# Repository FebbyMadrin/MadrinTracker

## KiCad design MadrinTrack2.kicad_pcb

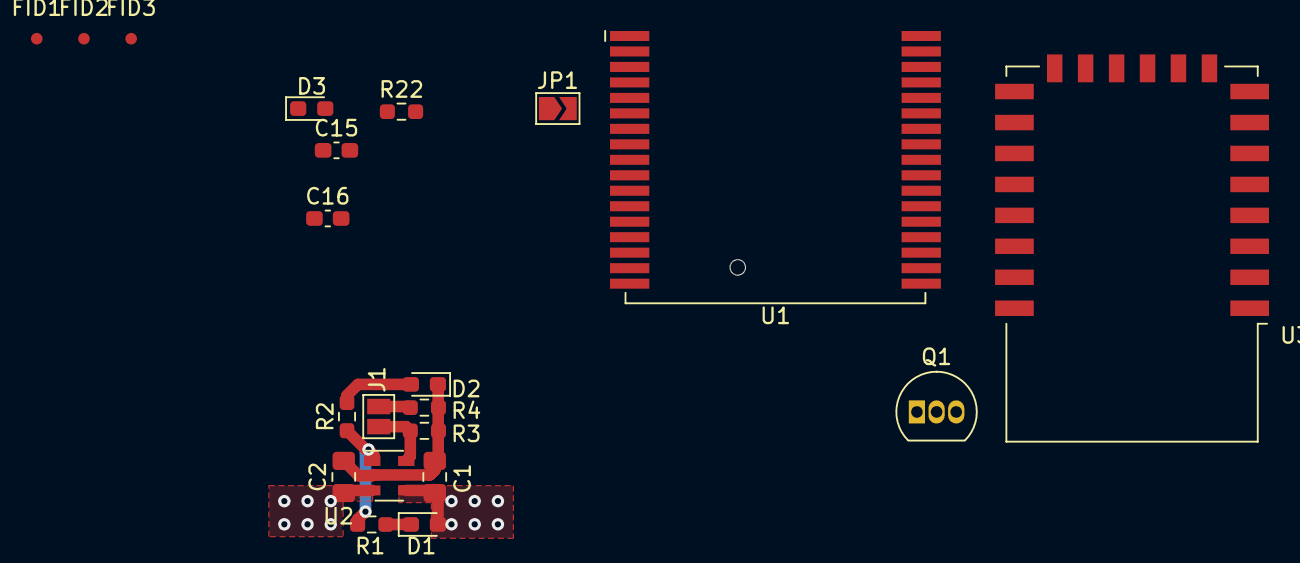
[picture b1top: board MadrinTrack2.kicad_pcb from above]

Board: 4 copper layers, 21 parts (0 on the bottom side), 11 nets.

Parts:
C1: 10nF; C_0805_2012Metric_Pad1.18x1.45mm_HandSolder
C2: C_Small; C_0805_2012Metric_Pad1.18x1.45mm_HandSolder
C15: 10u; C_0603_1608Metric_Pad1.08x0.95mm_HandSolder
C16: 100n; C_0603_1608Metric_Pad1.08x0.95mm_HandSolder
D1, D2, D3: LED; LED_0603_1608Metric_Pad1.05x0.95mm_HandSolder
FID1, FID2, FID3: Fiducial; Fiducial_0.75mm_Mask1.5mm
J1: Jumper_NC_Small; SolderJumper-2_P1.3mm_Open_Pad1.0x1.5mm
JP1: Jumper_NC_Small; SolderJumper-2_P1.3mm_Open_TrianglePad1.0x1.5mm
Q1: 2N7000; TO-92_Inline
R1, R2: 450; R_0603_1608Metric_Pad0.98x0.95mm_HandSolder
R3: 10k; R_0603_1608Metric_Pad0.98x0.95mm_HandSolder
R4: 2.5k; R_0603_1608Metric_Pad0.98x0.95mm_HandSolder
R22: 1k5; R_0603_1608Metric_Pad0.98x0.95mm_HandSolder
U1: DWM1001; DecaWave_DWM1001
U2: MCP73831-2-OT; SOT-23-5
U3: ESP-12E

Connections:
+3V3: C2.1, JP1.2, U2.3
/VFlash: C15.1, C16.1, U1.12
GND: C1.2, C2.2, C15.2, C16.2, D2.1, JP1.1, R3.2, R4.2, U1.1, U1.11, U1.24, U1.34, U2.2
unnamed: C1.1, D1.2, U2.4
unnamed: D1.1, R1.2
unnamed: D2.2, R2.1
unnamed: D3.2, R22.1
unnamed: J1.1, R3.1, U2.5
unnamed: J1.2, R4.1
unnamed: R1.1, R2.2, U2.1
unnamed: R22.2, U1.8

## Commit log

2021-03-25 adding fiducial
